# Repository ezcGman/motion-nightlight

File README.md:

# Motion Nightlight
This is one of my first self designed PCBs in KiCad. It's a very simple circuit which can be utilized to create a motion nightlight with a few low power LED strips. See some examples at the bottom.

## Credits
Shoutout to Quindor from QuinLED.info, the LED master himself. He tought me a lot about KiCad, PCB design and some more electrical engineering fundamentals! While I'm still miles away from being perfect, with his help I really feel confident in what I'm doing here!

## KiCad dependencies
It might happen that KiCad is missing my custom footprints. You can find and download them here and then add them to KiCad: https://github.com/ezcGman/andys-footprints

## Parts list
All these parts can be easily found on AliExpress (except the PCBs ;) ):

- 1x The PCB in this folder, printed e.g. at PCBWay
- 1x 3.2V LiFePO4 battery in AA form factor
- 1x AA battery holder for THT mounting
- The HC-SR501 PIR sensor. And because this also would act at day time, we also need:
- An LDR, a light-dependent resistor, which can be installed into the HC-SR501 to make it only act at night time. See that great video of Clive: https://www.youtube.com/watch?v=2dxhbXHYEG0
- 1x MOSFET. Probably most FETs (ha ha, MOSt FETs... ha ha) are fine, just pay attention that the thermal pad is connected to **drain**, as the MOSFET bed on the PCB is connected to drain! But I suggest the IRL3803 which has perfect specs for this application:
  - Max Drain-Source Voltage of 30V
  - Gate Threshold Voltage already of 1V
- 1x 0805 SMD capacitor of 10µF or bigger. But 0805 SMD caps are usually limited to ~40µF. So whatever u have around
- 1x 0805 SMD resistor of 10kΩ
- 4x 2.54mm double row pin headers. I chose angled headers, as it makes the whole thing more flat, so you can hide it behind something

## Tools list
### Required
- A soldering iron
- Soldering tin

### Optional
- For SMD components:
  - A hot air soldering/reflow station. However, it's only two and u have space around them, so they can be done with a soldering iron. Also the MOSFET can be technically soldered with an iron.
  - Solder paste
  - Tweezers

# Example installation:

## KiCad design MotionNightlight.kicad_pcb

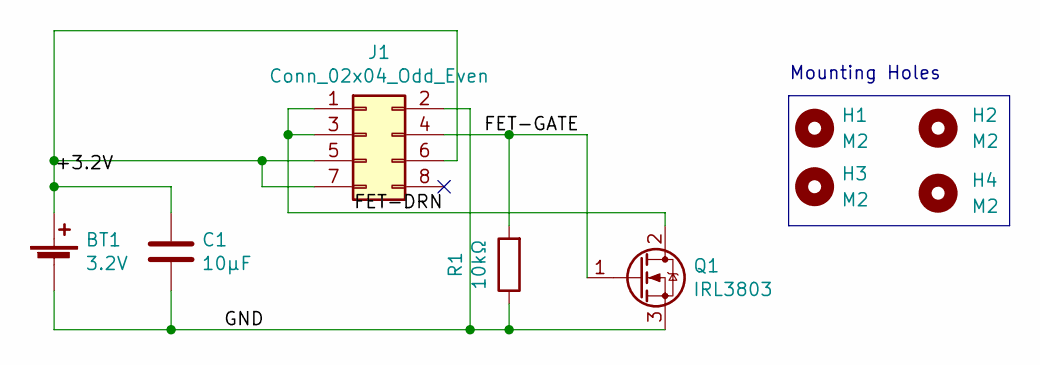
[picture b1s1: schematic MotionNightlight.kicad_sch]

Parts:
BT1: 3.2V; BatteryHolder_Keystone_2460_1xAA-removed-holes
C1: 10µF; C_0805_2012Metric_Pad1.18x1.45mm_HandSolder
H1, H2, H3, H4: M2; MountingHole_2.2mm_M2_Pad_Via
J1: Conn_02x04_Odd_Even; PinHeader_2x04_P2.54mm_Horizontal-Less-SilkScreen
Q1: IRL3803; TO-220-3_Vertical
R1: 10kΩ; R_0805_2012Metric_Pad1.20x1.40mm_HandSolder

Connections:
/+3.2V: BT1.1 (+), C1.1, J1.5, J1.6, J1.7
/FET-DRN: J1.1, J1.3, Q1.2 (D)
/FET-GATE: J1.4, Q1.1 (G), R1.2
/GND: BT1.2 (-), C1.2, J1.2, Q1.3 (S), R1.1

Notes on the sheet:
Mounting Holes

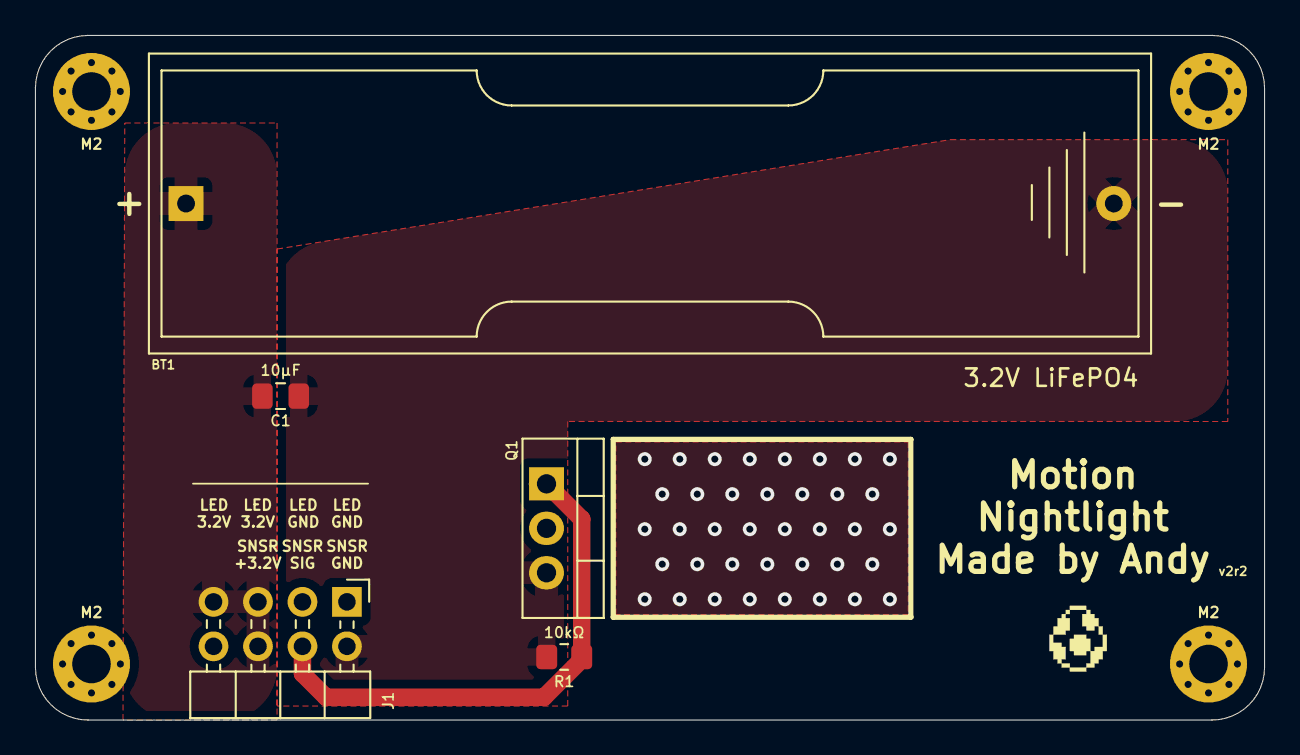
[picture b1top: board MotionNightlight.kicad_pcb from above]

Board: 2 copper layers, 70.2 x 39.1 mm, 9 parts (0 on the bottom side), 4 nets.

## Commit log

2021-06-06 Added photos
2021-06-06 Re-added photos
2021-06-06 Moved pictures into folder
2021-06-06 Added more pictures
2021-06-30 v2r1
2022-02-11 v2r2: Some silkscreen updates, moved the pin header
